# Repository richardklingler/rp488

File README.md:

# RP488 USB-GPIB Adapter

This project is an RP2350-based USB GPIB adapter.

## USB identifiers

- Vendor ID: `0x1209`
- Product ID: `0x5305`

## Hardware target

- Raspberry Pi Pico 2 W, RP2354
- SN75160B data transceiver
- SN75161B control transceiver
- GPIB bus interface using negative-true logic

## Test

The design was tested with a Raspberry Pi Pico 2 W board and an attached Yokogawa DL1540C 4-channel scope.
I was able to control the scope and download a binary screenshot as TIFF on macOS 27 with a simple Python script located in folder "test".

Waveform screenshot taken via binary GPIB transfer:

## Hardware

The firmware was tested with the Raspberry Pico 2 W development board and an external GPIB transceiver board.
Firmware should work with all RP2350 variants, including the new RP2354 with built-in 2MB flash.

Hardware design is of course made with KiCAD and is curretnly in the works.

You find the hardware related files in the "Hardware" folder.

## Firmware goals

- CDC ACM serial interface on USB
- Prologix-compatible ASCII command set
- Framed binary mode for large block transfers
- Controller-in-charge operation
- Serial poll and SRQ support
- Bus-safe handshake sequencing and timeout handling

## Build notes

Use the Pico SDK and configure `PICO_SDK_PATH` before generating the build files:

```bash
export PICO_SDK_PATH=/path/to/pico-sdk
cmake -S . -B build
cmake --build build
```

The generated binary is intended for the Pico 2 W with the GPIB interface board described in the implementation guide.

## License

Original hardware design files use CERN-OHL-S-2.0; firmware and software use
MIT. See [LICENSE.md](LICENSE.md) for scope details and links to the license
texts. Third-party materials retain their own licenses.

## Binary block transfers

The firmware supports streaming IEEE definite-length blocks over the CDC
serial connection without buffering the full payload in Pico RAM:

- Send the instrument's block-data query as a normal text line.
- Send `++bin read <maxlen>` to read the response. The adapter forwards the
	`#<digits><length>` header followed by exactly that many payload bytes. The
	limit is capped at 16 MiB.
- For a binary write, send `++bin write <len>` as a line, followed by exactly
	`<len>` raw bytes. The final byte is sent with EOI; no EOS characters are
	appended.

These transfers are binary, not terminal text. Use a serial client that can
read and write exact byte counts; do not rely on a terminal application's
line-oriented display for waveform data.

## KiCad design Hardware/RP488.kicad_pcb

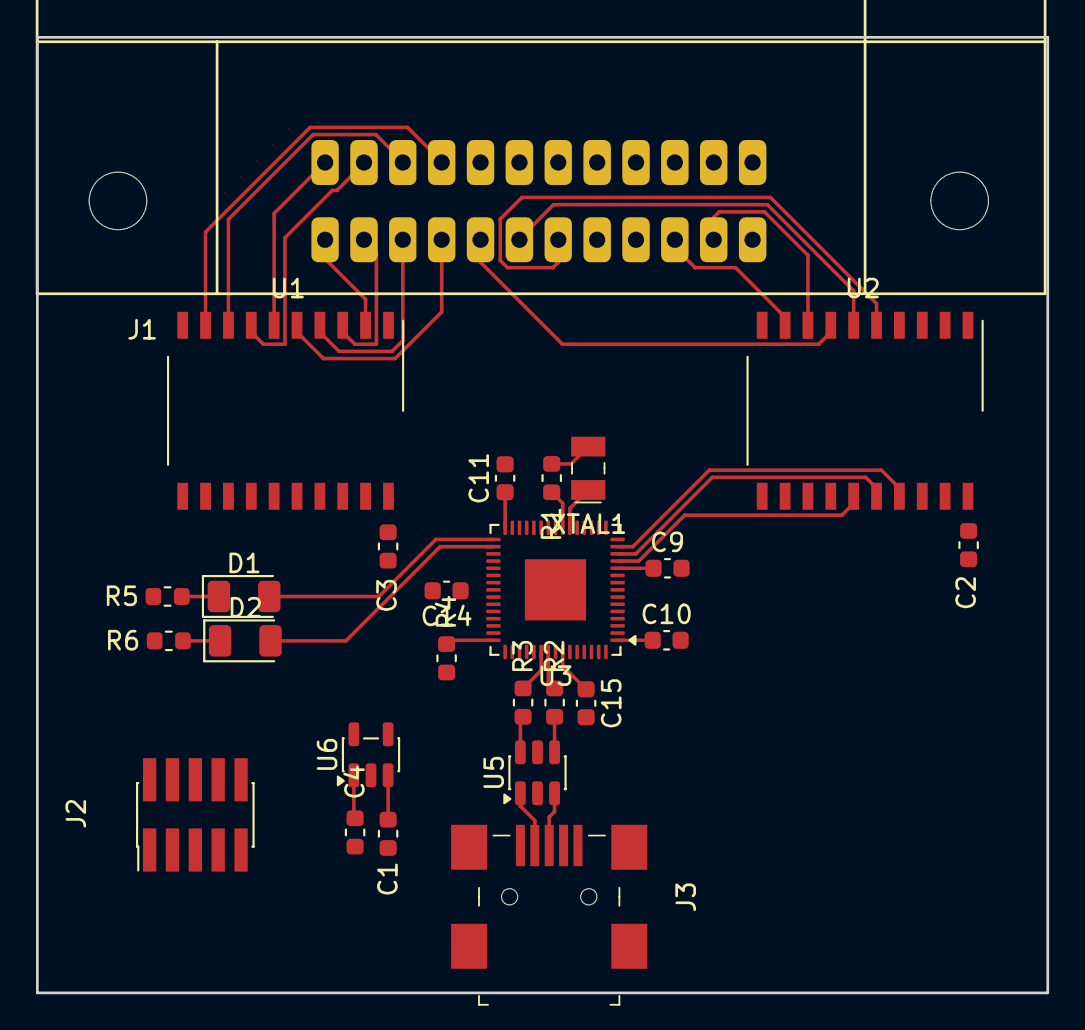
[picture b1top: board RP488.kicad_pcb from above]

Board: 2 copper layers, 56.1 x 53.1 mm, 26 parts (0 on the bottom side), 55 nets.

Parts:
C1, C2, C3, C9, C10, C11, C14, C15: 100n; C_0603_1608Metric
C4: 1u; C_0603_1608Metric
D1, D2: LED; LED_1206_3216Metric
J1: GPIB; 5553811
J2: SWD; PinHeader_2x05_P1.27mm_Vertical_SMD
J3: USB Mini; USB_Mini_B_Female_690-005-299-043
R1, R5, R6: 1K; R_0603_1608Metric
R2, R3: 27R; R_0603_1608Metric
R4: 33R; R_0603_1608Metric
U1: SN75160; SO-20_12.8x7.5mm_P1.27mm
U2: SN75161; SO-20_12.8x7.5mm_P1.27mm
U3: RP2354A; QFN-60-1EP_7x7mm_P0.4mm_EP3.4x3.4mm
U5: USBLC6-2SC6; SOT-23-6
U6: LD3985M33R_SOT23; SOT-23-5
XTAL1: 12MHz; SMD-2_3.2x1.5mm

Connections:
+3V3: C9.1, C10.1, C11.1, C14.1, C15.1, J2.1, R4.2, U3.1 (IOVDD), U3.11 (IOVDD), U3.20 (IOVDD), U3.26 (RUN), U3.30 (IOVDD), U3.38 (IOVDD), U3.44 (ADC_AVDD), U3.45 (IOVDD), U3.49 (VREG_VIN), U3.53 (USB_OTP_VDD), U3.54 (QSPI_IOVDD), U6.5 (VOUT)
+5V: C1.1, C2.1, C3.1, C4.1, J3.1, U1.20 (VCC), U2.20 (VCC), U5.5 (VBUS), U6.1 (VIN), U6.3 (INH)
/ATN: J1.11, U2.8 (ATN)
/DAV: J1.6, U2.6 (DAV)
/DIO1: J1.1, U1.2 (B1)
/DIO2: J1.2, U1.3 (B2)
/DIO3: J1.3, U1.4 (B3)
/DIO4: J1.4, U1.5 (B4)
/DIO5: J1.13, U1.6 (B5)
/DIO6: J1.14, U1.7 (B6)
/DIO7: J1.15, U1.8 (B7)
/DIO8: J1.16, U1.9 (B8)
/EOI: J1.5, U2.7 (EOI)
/IFC: J1.9, U2.3 (IFC)
/NDAC: J1.8, U2.4 (NDAC)
/NRFD: J1.7, U2.5 (NRFD)
/REN: J1.17, U2.2 (REN)
/SRQ: J1.10, U2.9 (SRQ)
/SWDCLK: J2.4, U3.24 (SWCLK)
/SWDIO: J2.2, U3.25 (SWDIO)
GNDD: C1.2, C2.2, C3.2, C4.2, C9.2, C10.2, C11.2, C14.2, C15.2, J1.18, J1.19, J1.20, J1.21, J1.22, J1.23, J1.24, J2.3, J2.5, J3.5, J3.SH, R5.2, R6.2, U1.10 (GND), U2.10 (GND), U3.47 (VREG_PGND), U3.61 (GND), U5.2 (GND), U6.2 (GND)
unnamed: R1.1, XTAL1.2
unnamed: D1.2 (A), U3.31 (GPIO19)
unnamed: D1.1 (K), R5.1
unnamed: D2.2 (A), U3.32 (GPIO20)
unnamed: D2.1 (K), R6.1
unnamed: J3.2, U5.1 (IO1)
unnamed: J3.3, U5.3 (IO2)
unnamed: R2.1, U5.4 (IO2)
unnamed: R3.1, U5.6 (IO1)
unnamed: U1.19 (D1), U3.2 (GPIO0)
unnamed: U1.18 (D2), U3.3 (GPIO1)
unnamed: U1.17 (D3), U3.4 (GPIO2)
unnamed: U1.16 (D4), U3.5 (GPIO3)
unnamed: U1.15 (D5), U3.7 (GPIO4)
unnamed: U1.14 (D6), U3.8 (GPIO5)
unnamed: U1.13 (D7), U3.9 (GPIO6)
unnamed: U1.12 (D8), U3.10 (GPIO7)
unnamed: U1.11 (PE), U3.28 (GPIO17)
unnamed: U1.1 (TE), U2.1 (TE), U3.27 (GPIO16)
unnamed: U2.11 (DC), U3.29 (GPIO18)
unnamed: U2.15 (DAV), U3.12 (GPIO8)
unnamed: U2.16 (NRFD), U3.13 (GPIO9)
unnamed: U2.17 (NDAC), U3.14 (GPIO10)
unnamed: U2.14 (EOI), U3.15 (GPIO11)
unnamed: U2.13 (ATN), U3.16 (GPIO12)
unnamed: U2.12 (SRQ), U3.17 (GPIO13)
unnamed: U2.18 (IFC), U3.18 (GPIO14)
unnamed: U2.19 (REN), U3.19 (GPIO15)
unnamed: R3.2, U3.51 (USB_DM)
unnamed: R2.2, U3.52 (USB_DP)
unnamed: R4.1, U3.46 (VREG_AVDD)
unnamed: U3.6 (DVDD), U3.23 (DVDD), U3.39 (DVDD), U3.50 (VREG_FB)
unnamed: U3.21 (XIN), XTAL1.1
unnamed: R1.2, U3.22 (XOUT)
